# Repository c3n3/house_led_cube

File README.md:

# house_led_cube
LED Cube
digitalWrite

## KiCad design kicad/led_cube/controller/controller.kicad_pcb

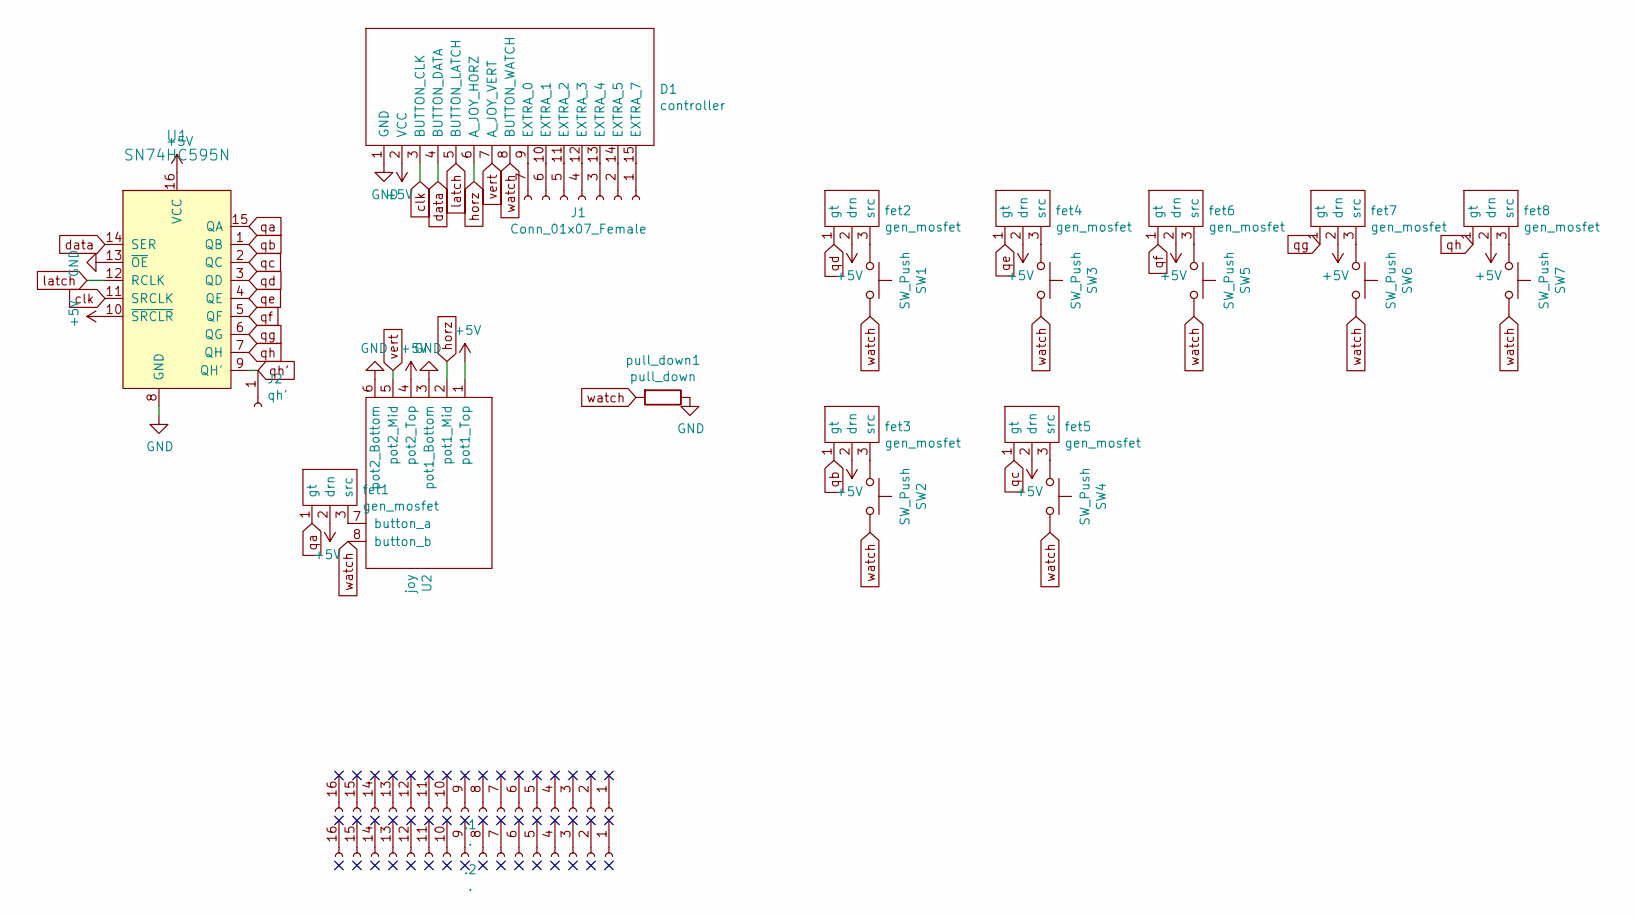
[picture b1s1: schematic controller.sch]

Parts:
.1, .2: .; proto
D1: controller; 15pin_controller
J1: Conn_01x07_Female; PinHeader_1x07_P2.54mm_Vertical
J2: qh'; PinHeader_1x01_P2.54mm_Horizontal
SW1, SW2, SW3, SW4, SW5, SW6, SW7: SW_Push; button
U1: SN74HC595N; MPN SN74HC595N; Digi-Key_PN 296-1600-5-ND
U2: joy
fet1, fet2, fet3, fet4, fet5, fet6, fet7, fet8: gen_mosfet; gen_fet
pull_down1: pull_down; R_Axial_DIN0207_L6.3mm_D2.5mm_P10.16mm_Horizontal

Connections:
+5V: D1.2 (VCC), U1.10 (~SRCLR), U1.16 (VCC), U2.1 (pot1_Top), U2.4 (pot2_Top), fet1.2 (drn), fet2.2 (drn), fet3.2 (drn), fet4.2 (drn), fet5.2 (drn), fet6.2 (drn), fet7.2 (drn), fet8.2 (drn)
GND: D1.1 (GND), U1.8 (GND), U1.13 (~OE), U2.3 (pot1_Bottom), U2.6 (pot2_Bottom), pull_down1.1
unnamed: D1.9 (EXTRA_0), J1.7
unnamed: D1.10 (EXTRA_1), J1.6
unnamed: D1.11 (EXTRA_2), J1.5
unnamed: D1.12 (EXTRA_3), J1.4
unnamed: D1.13 (EXTRA_4), J1.3
unnamed: D1.14 (EXTRA_5), J1.2
unnamed: D1.15 (EXTRA_7), J1.1
unnamed: SW1.1, fet2.3 (src)
unnamed: SW2.1, fet3.3 (src)
unnamed: SW3.1, fet4.3 (src)
unnamed: SW4.1, fet5.3 (src)
unnamed: SW5.1, fet6.3 (src)
unnamed: SW6.1, fet7.3 (src)
unnamed: SW7.1, fet8.3 (src)
unnamed: U2.7 (button_a), fet1.3 (src)
clk: D1.3 (BUTTON_CLK), U1.11 (SRCLK)
data: D1.4 (BUTTON_DATA), U1.14 (SER)
horz: D1.6 (A_JOY_HORZ), U2.2 (pot1_Mid)
latch: D1.5 (BUTTON_LATCH), U1.12 (RCLK)
qa: U1.15 (QA), fet1.1 (gt)
qb: U1.1 (QB), fet3.1 (gt)
qc: U1.2 (QC), fet5.1 (gt)
qd: U1.3 (QD), fet2.1 (gt)
qe: U1.4 (QE), fet4.1 (gt)
qf: U1.5 (QF), fet6.1 (gt)
qg: U1.6 (QG), fet7.1 (gt)
qh: U1.7 (QH), fet8.1 (gt)
qh': J2.1, U1.9 (QH')
vert: D1.7 (A_JOY_VERT), U2.5 (pot2_Mid)
watch: D1.8 (BUTTON_WATCH), SW1.2, SW2.2, SW3.2, SW4.2, SW5.2, SW6.2, SW7.2, U2.8 (button_b), pull_down1.2

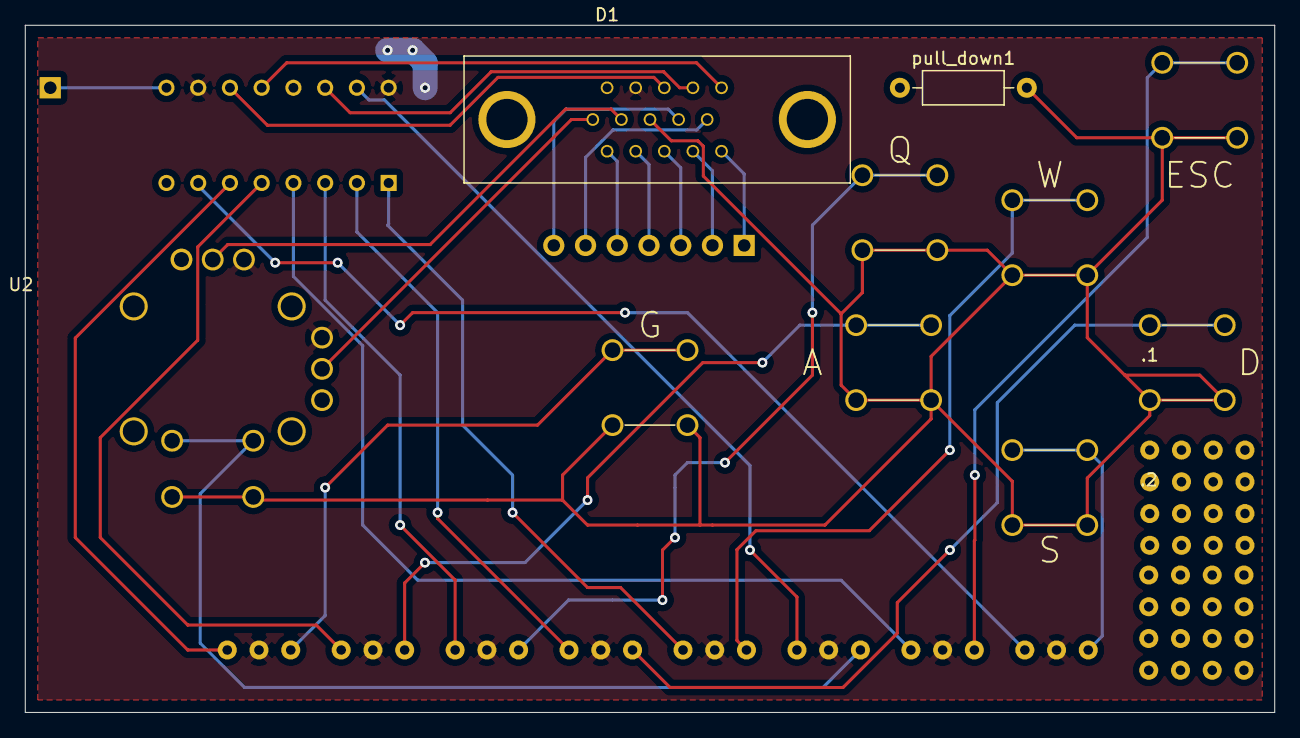
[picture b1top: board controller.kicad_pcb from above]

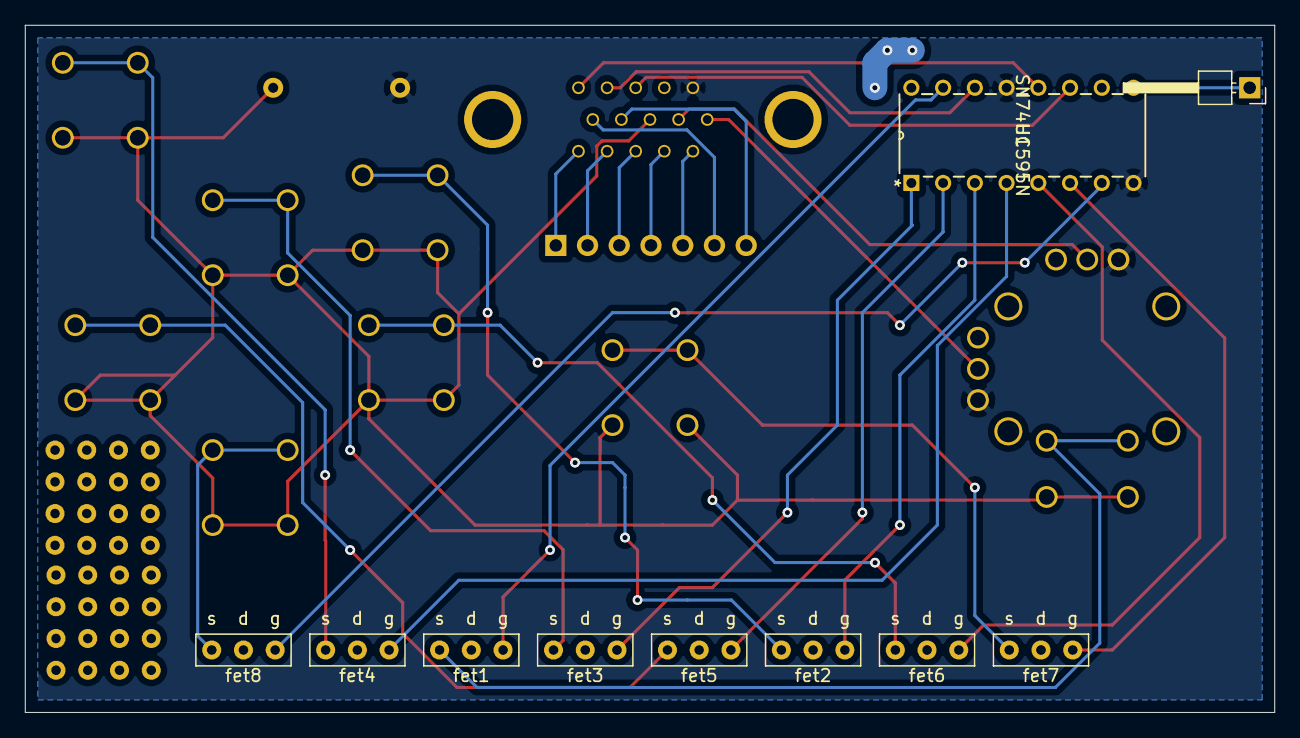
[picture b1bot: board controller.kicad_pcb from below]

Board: 2 copper layers, 100.0 x 55.0 mm, 23 parts (10 on the bottom side), 32 nets.

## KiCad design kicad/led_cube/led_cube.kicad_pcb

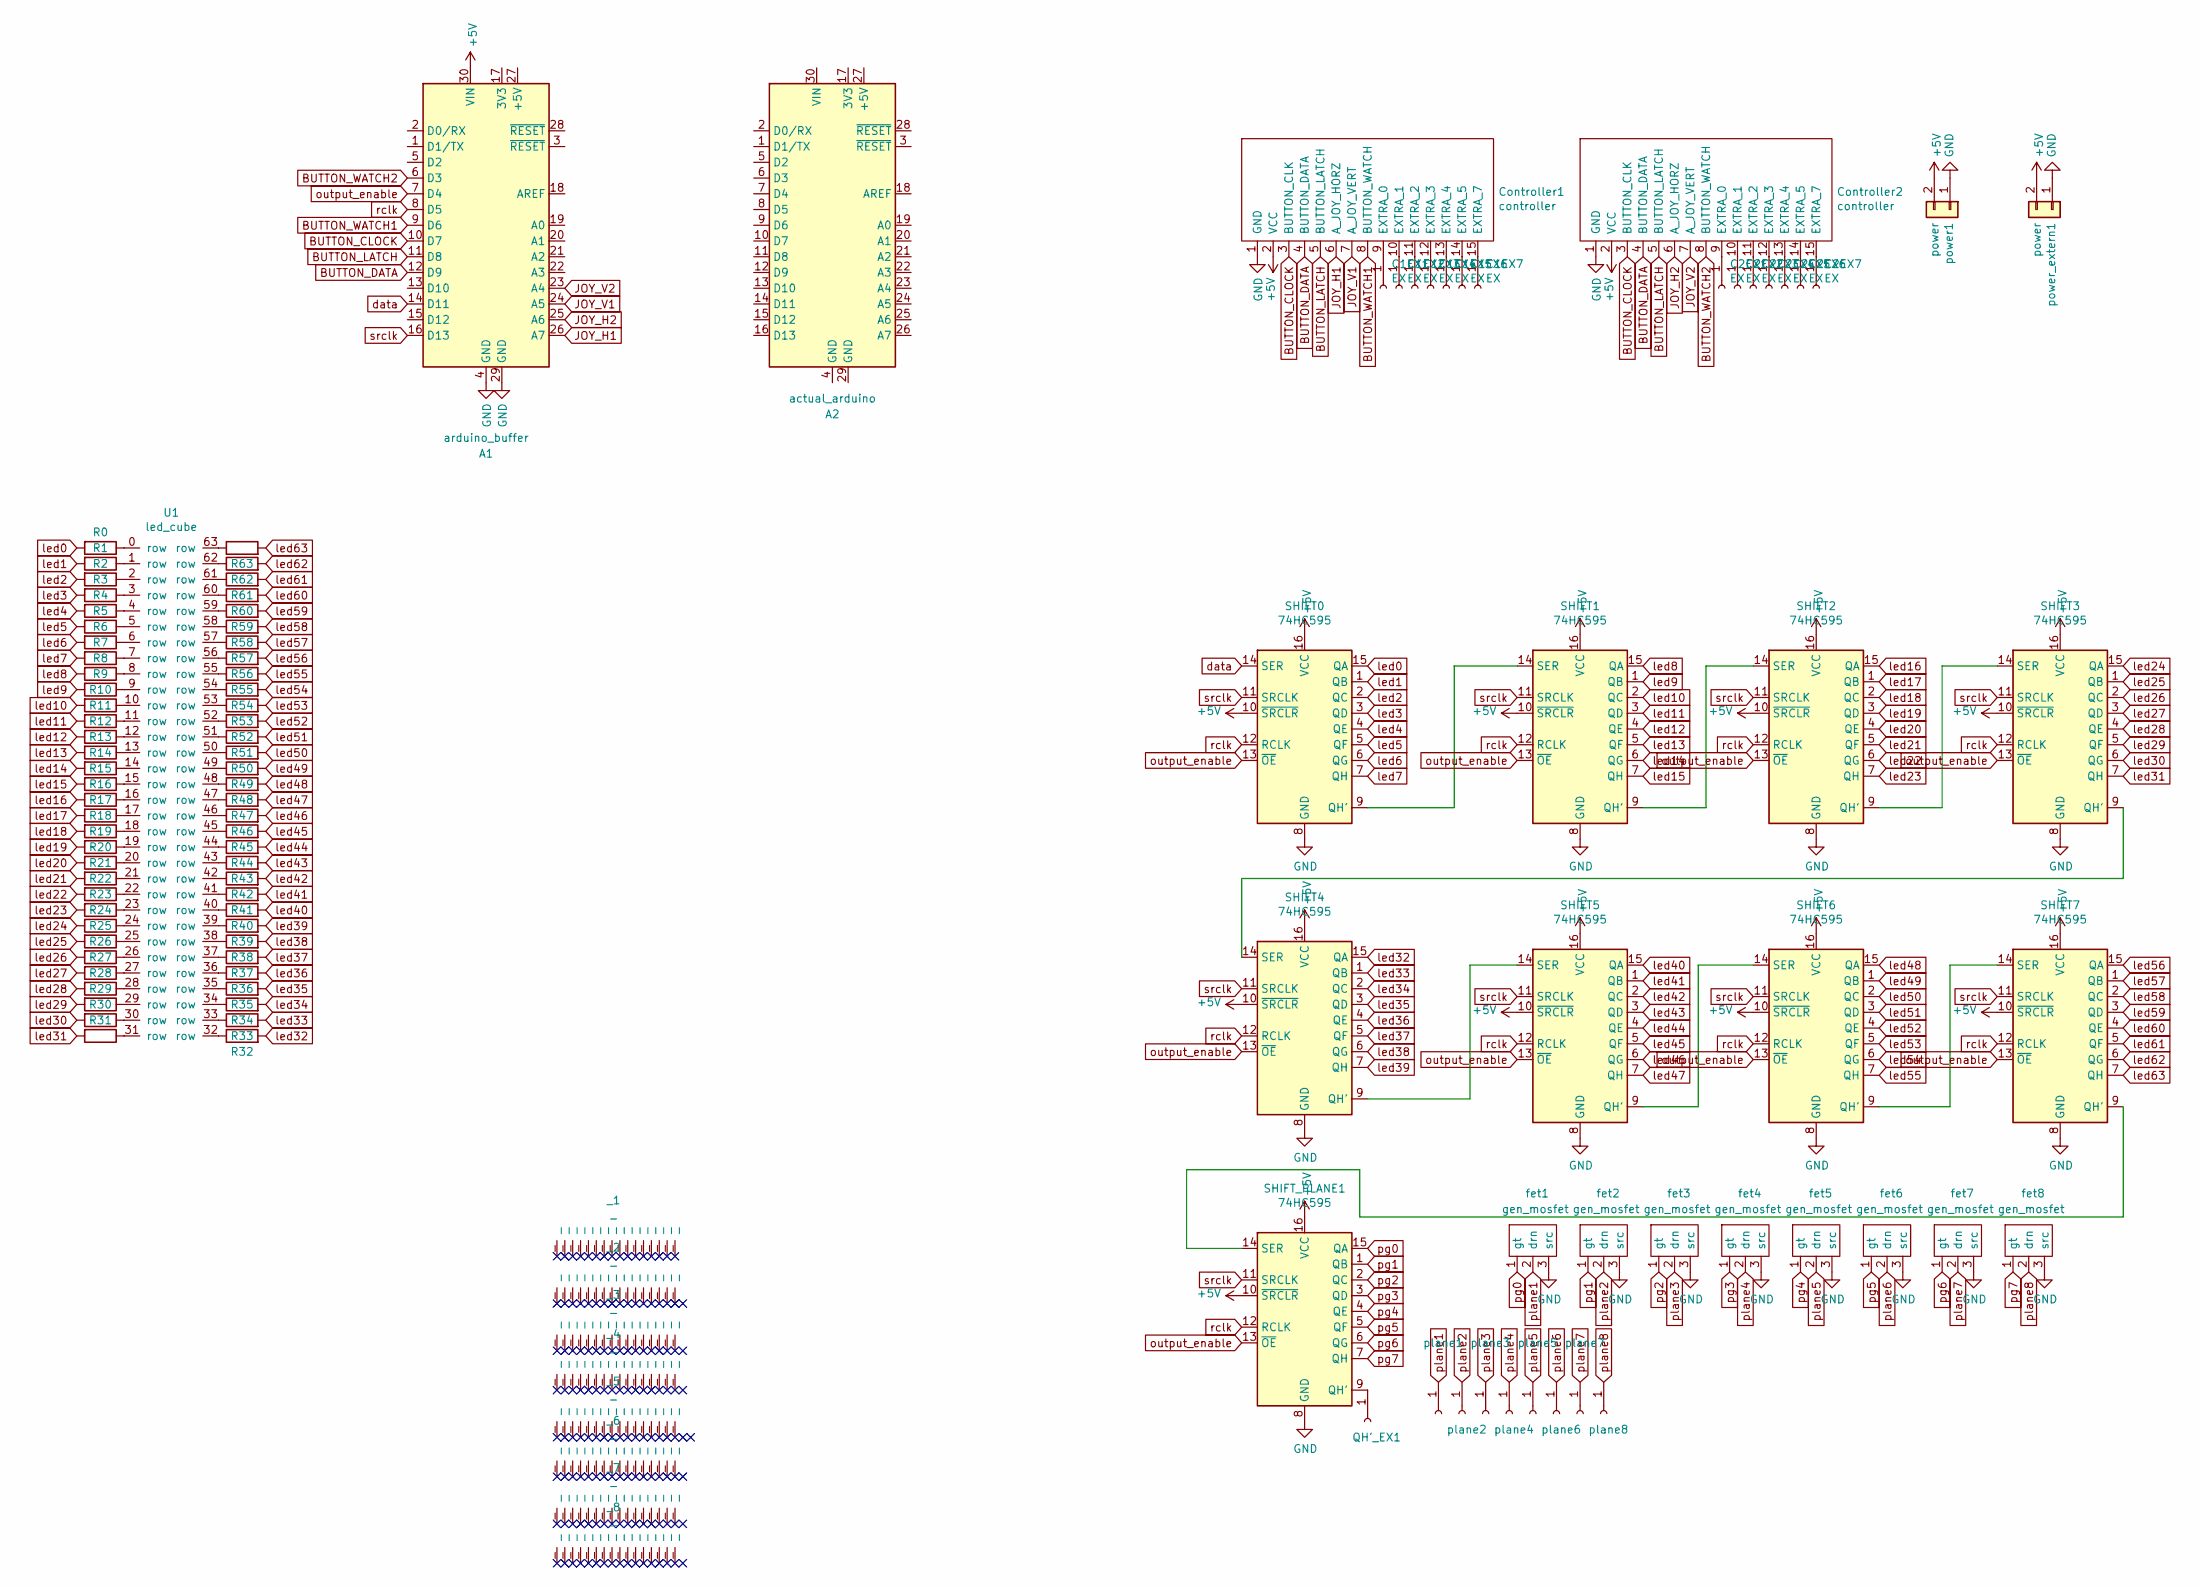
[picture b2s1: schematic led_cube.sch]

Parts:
A1: arduino_buffer; nano_buffer
A2: actual_arduino; nano
C1EX1, C1EX2, C1EX3, C1EX4, C1EX5, C1EX6, C1EX7, C2EX1, C2EX2, C2EX3, C2EX4, C2EX5, C2EX6, C2EX7: EX; PinHeader_1x01_P2.54mm_Vertical
Controller1, Controller2: controller; 15pin_controller
QH'_EX1: PinHeader_1x01_P2.54mm_Vertical
R0, R1, R2, R3, R4, R5, R6, R7, R8, R9, R10, R11, R12, R13, R14, R15, R16, R17, R18, R19, R20, R21, R22, R23, R24, R25, R26, R27, R28, R29, R30, R31, R32, R33, R34, R35, R36, R37, R38, R39, R40, R41, R42, R43, R44, R45, R46, R47, R48, R49, R50, R51, R52, R53, R54, R55, R56, R57, R58, R59, R60, R61, R62, R63: R_Axial_DIN0207_L6.3mm_D2.5mm_P7.62mm_Horizontal
SHIFT0, SHIFT1, SHIFT2, SHIFT3, SHIFT4, SHIFT5, SHIFT6, SHIFT7: 74HC595; SN74HC595N
SHIFT_PLANE1: 74HC595; SN74HC595N
U1: led_cube
_1, _2, _3, _4, _5, _6, _7, _8: _; proto
fet1, fet2, fet3, fet4, fet5, fet6, fet7, fet8: gen_mosfet; gen_fet
plane1, plane2, plane3, plane4, plane5, plane6, plane7, plane8: PinHeader_1x01_P2.54mm_Vertical
power1: power
power_extern1: power

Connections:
+5V: A1.30 (VIN), Controller1.2 (VCC), Controller2.2 (VCC), SHIFT0.10 (~SRCLR), SHIFT0.16 (VCC), SHIFT1.10 (~SRCLR), SHIFT1.16 (VCC), SHIFT2.10 (~SRCLR), SHIFT2.16 (VCC), SHIFT3.10 (~SRCLR), SHIFT3.16 (VCC), SHIFT4.10 (~SRCLR), SHIFT4.16 (VCC), SHIFT5.10 (~SRCLR), SHIFT5.16 (VCC), SHIFT6.10 (~SRCLR), SHIFT6.16 (VCC), SHIFT7.10 (~SRCLR), SHIFT7.16 (VCC), SHIFT_PLANE1.10 (~SRCLR), SHIFT_PLANE1.16 (VCC), power1.2, power_extern1.2
BUTTON_CLOCK: A1.10 (D7), Controller1.3 (BUTTON_CLK), Controller2.3 (BUTTON_CLK)
BUTTON_DATA: A1.12 (D9), Controller1.4 (BUTTON_DATA), Controller2.4 (BUTTON_DATA)
BUTTON_LATCH: A1.11 (D8), Controller1.5 (BUTTON_LATCH), Controller2.5 (BUTTON_LATCH)
BUTTON_WATCH1: A1.9 (D6), Controller1.8 (BUTTON_WATCH)
BUTTON_WATCH2: A1.6 (D3), Controller2.8 (BUTTON_WATCH)
GND: A1.4 (GND), A1.29 (GND), Controller1.1 (GND), Controller2.1 (GND), SHIFT0.8 (GND), SHIFT1.8 (GND), SHIFT2.8 (GND), SHIFT3.8 (GND), SHIFT4.8 (GND), SHIFT5.8 (GND), SHIFT6.8 (GND), SHIFT7.8 (GND), SHIFT_PLANE1.8 (GND), fet1.3 (src), fet2.3 (src), fet3.3 (src), fet4.3 (src), fet5.3 (src), fet6.3 (src), fet7.3 (src), fet8.3 (src), power1.1, power_extern1.1
JOY_H1: A1.26 (A7), Controller1.6 (A_JOY_HORZ)
JOY_H2: A1.25 (A6), Controller2.6 (A_JOY_HORZ)
JOY_V1: A1.24 (A5), Controller1.7 (A_JOY_VERT)
JOY_V2: A1.23 (A4), Controller2.7 (A_JOY_VERT)
unnamed: C1EX1.1, Controller1.9 (EXTRA_0)
unnamed: C1EX2.1, Controller1.10 (EXTRA_1)
unnamed: C1EX3.1, Controller1.11 (EXTRA_2)
unnamed: C1EX4.1, Controller1.12 (EXTRA_3)
unnamed: C1EX5.1, Controller1.13 (EXTRA_4)
unnamed: C1EX6.1, Controller1.14 (EXTRA_5)
unnamed: C1EX7.1, Controller1.15 (EXTRA_7)
unnamed: C2EX1.1, Controller2.9 (EXTRA_0)
unnamed: C2EX2.1, Controller2.10 (EXTRA_1)
unnamed: C2EX3.1, Controller2.11 (EXTRA_2)
unnamed: C2EX4.1, Controller2.12 (EXTRA_3)
unnamed: C2EX5.1, Controller2.13 (EXTRA_4)
unnamed: C2EX6.1, Controller2.14 (EXTRA_5)
unnamed: C2EX7.1, Controller2.15 (EXTRA_7)
unnamed: QH'_EX1.1, SHIFT_PLANE1.9 (QH')
unnamed: R0.1, U1.0
unnamed: R1.1, U1.1
unnamed: R2.1, U1.2
unnamed: R3.1, U1.3
unnamed: R4.1, U1.4
unnamed: R5.1, U1.5
unnamed: R6.1, U1.6
unnamed: R7.1, U1.7
unnamed: R8.1, U1.8
unnamed: R9.1, U1.9
unnamed: R10.1, U1.10
unnamed: R11.1, U1.11
unnamed: R12.1, U1.12
unnamed: R13.1, U1.13
unnamed: R14.1, U1.14
unnamed: R15.1, U1.15
unnamed: R16.1, U1.16
unnamed: R17.1, U1.17
unnamed: R18.1, U1.18
unnamed: R19.1, U1.19
unnamed: R20.1, U1.20
unnamed: R21.1, U1.21
unnamed: R22.1, U1.22
unnamed: R23.1, U1.23
unnamed: R24.1, U1.24
unnamed: R25.1, U1.25
unnamed: R26.1, U1.26
unnamed: R27.1, U1.27
unnamed: R28.1, U1.28
unnamed: R29.1, U1.29
unnamed: R30.1, U1.30
unnamed: R31.1, U1.31
unnamed: R32.1, U1.32
unnamed: R33.1, U1.33
unnamed: R34.1, U1.34
unnamed: R35.1, U1.35
unnamed: R36.1, U1.36
unnamed: R37.1, U1.37
unnamed: R38.1, U1.38
unnamed: R39.1, U1.39
unnamed: R40.1, U1.40
unnamed: R41.1, U1.41
unnamed: R42.1, U1.42
unnamed: R43.1, U1.43
unnamed: R44.1, U1.44
unnamed: R45.1, U1.45
unnamed: R46.1, U1.46
unnamed: R47.1, U1.47
unnamed: R48.1, U1.48
unnamed: R49.1, U1.49
unnamed: R50.1, U1.50
unnamed: R51.1, U1.51
unnamed: R52.1, U1.52
unnamed: R53.1, U1.53
unnamed: R54.1, U1.54
unnamed: R55.1, U1.55
unnamed: R56.1, U1.56
unnamed: R57.1, U1.57
unnamed: R58.1, U1.58
unnamed: R59.1, U1.59
unnamed: R60.1, U1.60
unnamed: R61.1, U1.61
unnamed: R62.1, U1.62
unnamed: R63.1, U1.63
unnamed: SHIFT0.9 (QH'), SHIFT1.14 (SER)
unnamed: SHIFT1.9 (QH'), SHIFT2.14 (SER)
unnamed: SHIFT2.9 (QH'), SHIFT3.14 (SER)
unnamed: SHIFT3.9 (QH'), SHIFT4.14 (SER)
unnamed: SHIFT4.9 (QH'), SHIFT5.14 (SER)
unnamed: SHIFT5.9 (QH'), SHIFT6.14 (SER)
unnamed: SHIFT6.9 (QH'), SHIFT7.14 (SER)
unnamed: SHIFT7.9 (QH'), SHIFT_PLANE1.14 (SER)
data: A1.14 (D11), SHIFT0.14 (SER)
led0: R0.2, SHIFT0.15 (QA)
led1: R1.2, SHIFT0.1 (QB)
led2: R2.2, SHIFT0.2 (QC)
led3: R3.2, SHIFT0.3 (QD)
led4: R4.2, SHIFT0.4 (QE)
led5: R5.2, SHIFT0.5 (QF)
led6: R6.2, SHIFT0.6 (QG)
led7: R7.2, SHIFT0.7 (QH)
led8: R8.2, SHIFT1.15 (QA)
led9: R9.2, SHIFT1.1 (QB)
led10: R10.2, SHIFT1.2 (QC)
led11: R11.2, SHIFT1.3 (QD)
led12: R12.2, SHIFT1.4 (QE)
led13: R13.2, SHIFT1.5 (QF)
led14: R14.2, SHIFT1.6 (QG)
led15: R15.2, SHIFT1.7 (QH)
led16: R16.2, SHIFT2.15 (QA)
led17: R17.2, SHIFT2.1 (QB)
led18: R18.2, SHIFT2.2 (QC)
led19: R19.2, SHIFT2.3 (QD)
led20: R20.2, SHIFT2.4 (QE)
led21: R21.2, SHIFT2.5 (QF)
led22: R22.2, SHIFT2.6 (QG)
led23: R23.2, SHIFT2.7 (QH)
led24: R24.2, SHIFT3.15 (QA)
led25: R25.2, SHIFT3.1 (QB)
led26: R26.2, SHIFT3.2 (QC)
led27: R27.2, SHIFT3.3 (QD)
led28: R28.2, SHIFT3.4 (QE)
led29: R29.2, SHIFT3.5 (QF)
led30: R30.2, SHIFT3.6 (QG)
led31: R31.2, SHIFT3.7 (QH)
led32: R32.2, SHIFT4.15 (QA)
led33: R33.2, SHIFT4.1 (QB)
led34: R34.2, SHIFT4.2 (QC)
led35: R35.2, SHIFT4.3 (QD)
led36: R36.2, SHIFT4.4 (QE)
led37: R37.2, SHIFT4.5 (QF)
led38: R38.2, SHIFT4.6 (QG)
led39: R39.2, SHIFT4.7 (QH)
led40: R40.2, SHIFT5.15 (QA)
led41: R41.2, SHIFT5.1 (QB)
led42: R42.2, SHIFT5.2 (QC)
led43: R43.2, SHIFT5.3 (QD)
led44: R44.2, SHIFT5.4 (QE)
led45: R45.2, SHIFT5.5 (QF)
led46: R46.2, SHIFT5.6 (QG)
led47: R47.2, SHIFT5.7 (QH)
led48: R48.2, SHIFT6.15 (QA)
led49: R49.2, SHIFT6.1 (QB)
led50: R50.2, SHIFT6.2 (QC)
led51: R51.2, SHIFT6.3 (QD)
led52: R52.2, SHIFT6.4 (QE)
led53: R53.2, SHIFT6.5 (QF)
led54: R54.2, SHIFT6.6 (QG)
led55: R55.2, SHIFT6.7 (QH)
led56: R56.2, SHIFT7.15 (QA)
led57: R57.2, SHIFT7.1 (QB)
led58: R58.2, SHIFT7.2 (QC)
led59: R59.2, SHIFT7.3 (QD)
led60: R60.2, SHIFT7.4 (QE)
led61: R61.2, SHIFT7.5 (QF)
led62: R62.2, SHIFT7.6 (QG)
led63: R63.2, SHIFT7.7 (QH)
output_enable: A1.7 (D4), SHIFT0.13 (~OE), SHIFT1.13 (~OE), SHIFT2.13 (~OE), SHIFT3.13 (~OE), SHIFT4.13 (~OE), SHIFT5.13 (~OE), SHIFT6.13 (~OE), SHIFT7.13 (~OE), SHIFT_PLANE1.13 (~OE)
pg0: SHIFT_PLANE1.15 (QA), fet1.1 (gt)
pg1: SHIFT_PLANE1.1 (QB), fet2.1 (gt)
pg2: SHIFT_PLANE1.2 (QC), fet3.1 (gt)
pg3: SHIFT_PLANE1.3 (QD), fet4.1 (gt)
pg4: SHIFT_PLANE1.4 (QE), fet5.1 (gt)
pg5: SHIFT_PLANE1.5 (QF), fet6.1 (gt)
pg6: SHIFT_PLANE1.6 (QG), fet7.1 (gt)
pg7: SHIFT_PLANE1.7 (QH), fet8.1 (gt)
plane1: fet1.2 (drn), plane1.1
plane2: fet2.2 (drn), plane2.1
plane3: fet3.2 (drn), plane3.1
plane4: fet4.2 (drn), plane4.1
plane5: fet5.2 (drn), plane5.1
plane6: fet6.2 (drn), plane6.1
plane7: fet7.2 (drn), plane7.1
plane8: fet8.2 (drn), plane8.1
rclk: A1.8 (D5), SHIFT0.12 (RCLK), SHIFT1.12 (RCLK), SHIFT2.12 (RCLK), SHIFT3.12 (RCLK), SHIFT4.12 (RCLK), SHIFT5.12 (RCLK), SHIFT6.12 (RCLK), SHIFT7.12 (RCLK), SHIFT_PLANE1.12 (RCLK)
srclk: A1.16 (D13), SHIFT0.11 (SRCLK), SHIFT1.11 (SRCLK), SHIFT2.11 (SRCLK), SHIFT3.11 (SRCLK), SHIFT4.11 (SRCLK), SHIFT5.11 (SRCLK), SHIFT6.11 (SRCLK), SHIFT7.11 (SRCLK), SHIFT_PLANE1.11 (SRCLK)

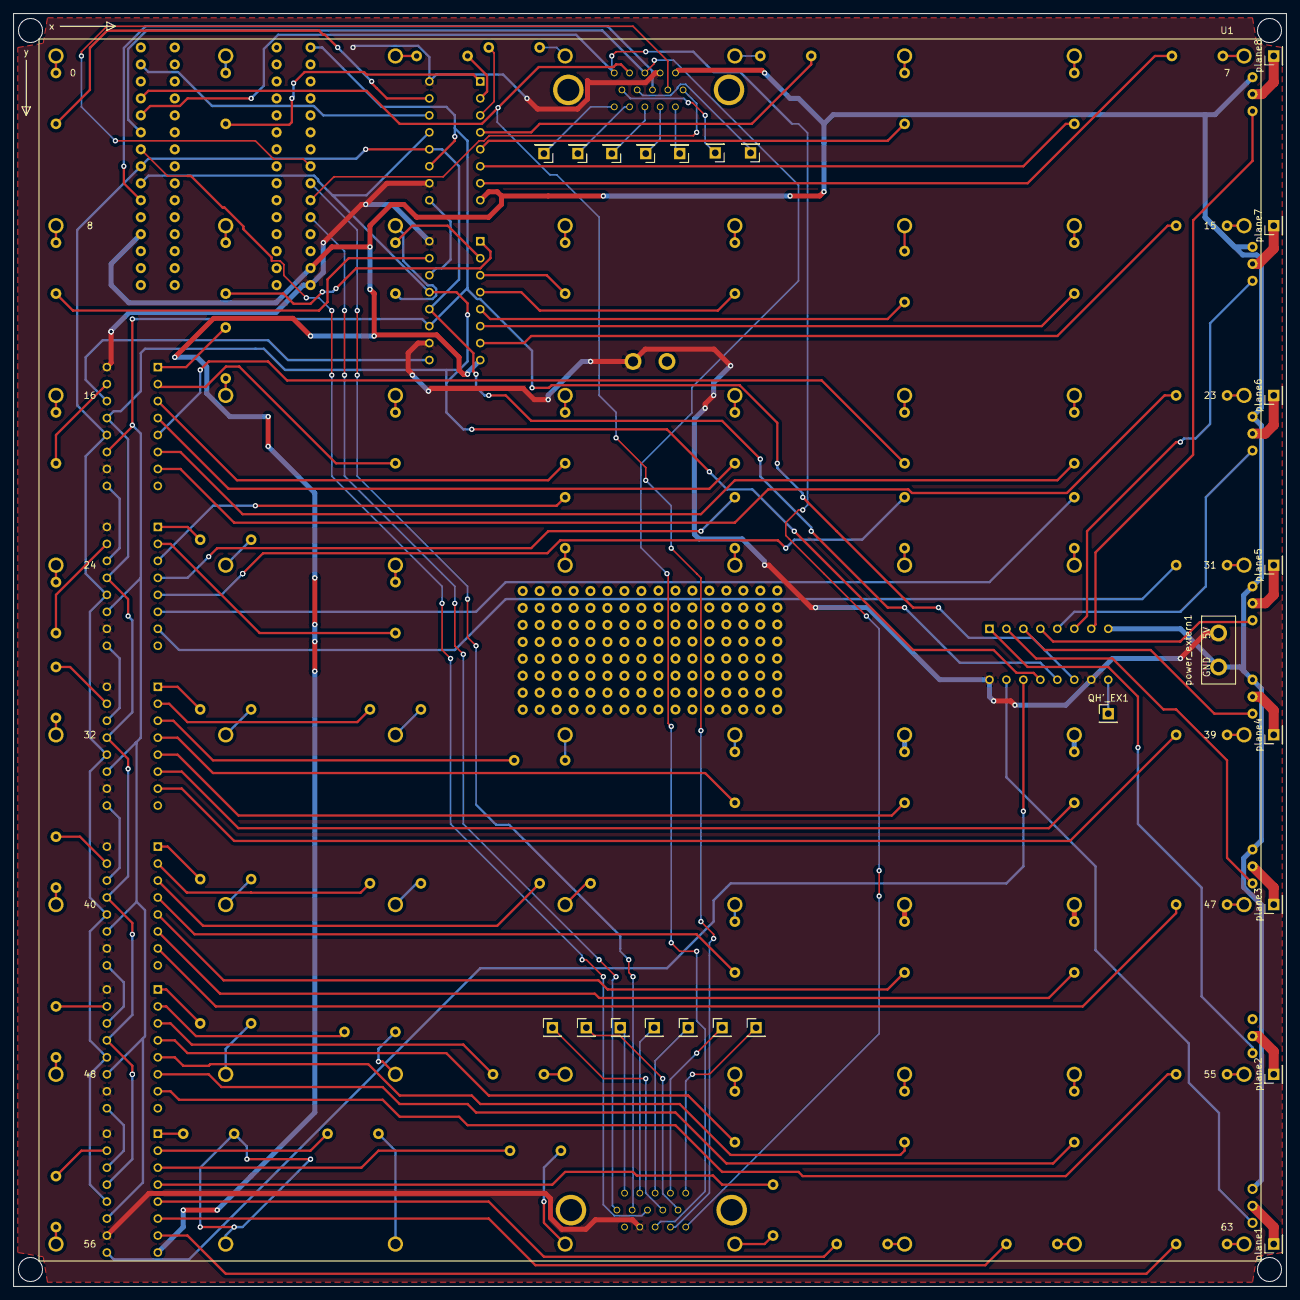
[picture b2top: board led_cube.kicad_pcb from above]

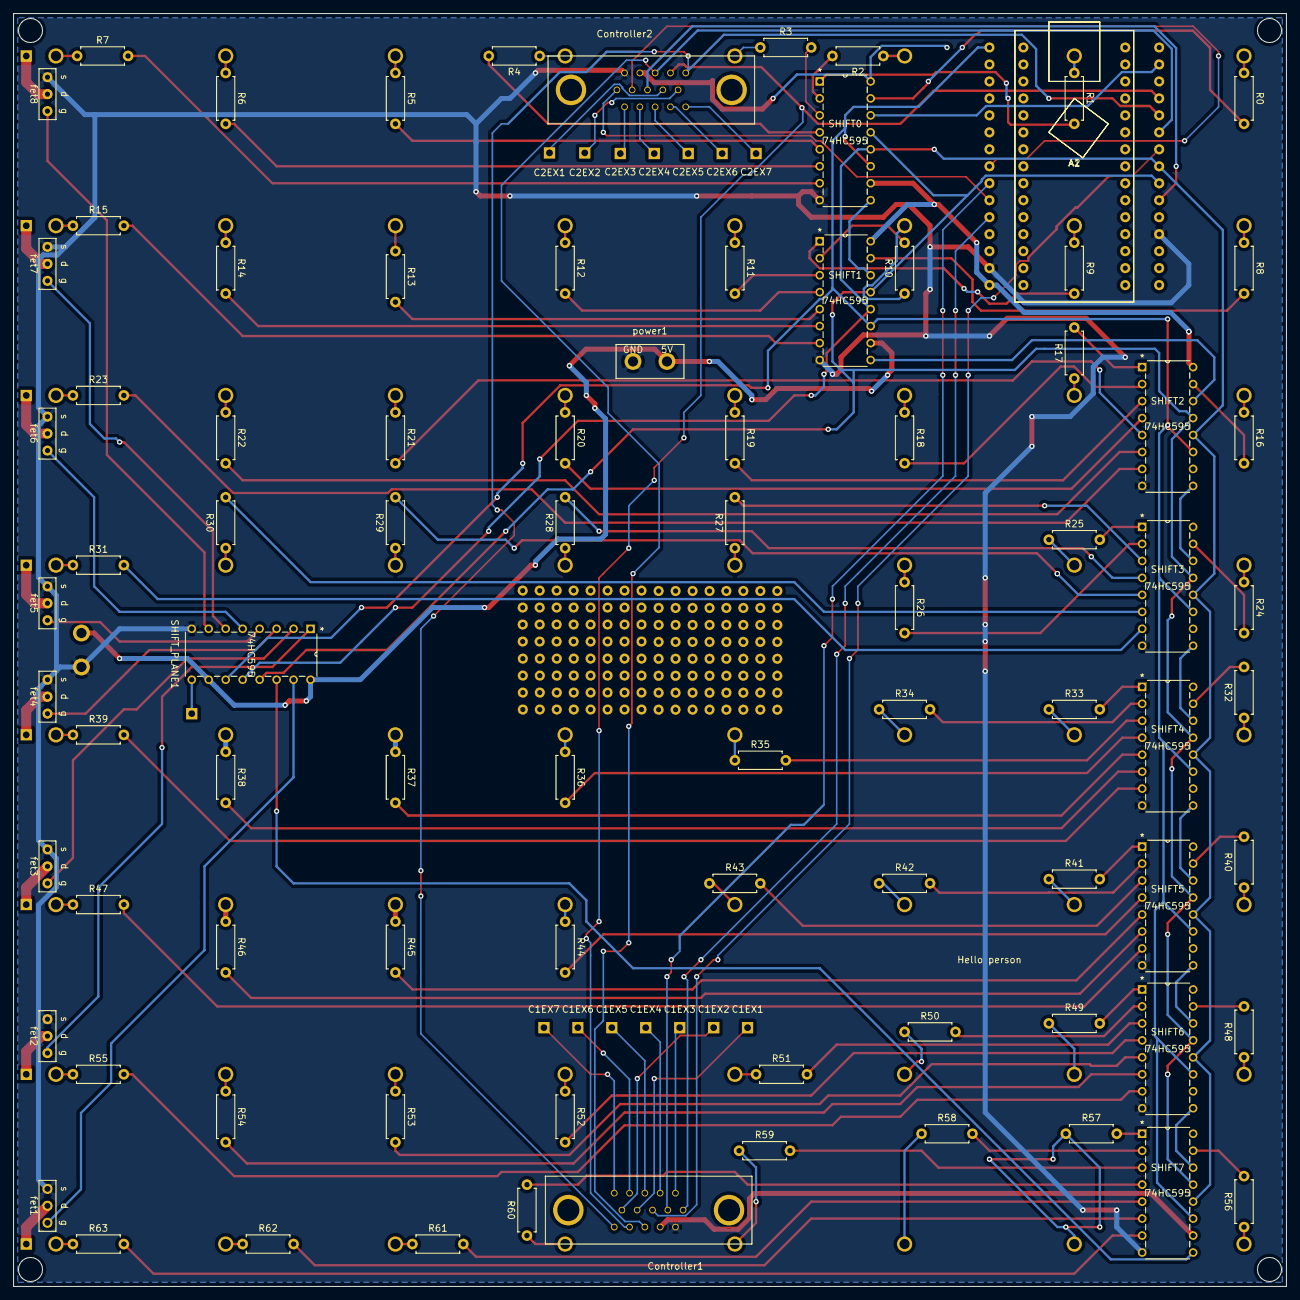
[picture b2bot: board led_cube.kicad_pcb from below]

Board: 2 copper layers, 190.5 x 190.5 mm, 119 parts (86 on the bottom side), 182 nets.

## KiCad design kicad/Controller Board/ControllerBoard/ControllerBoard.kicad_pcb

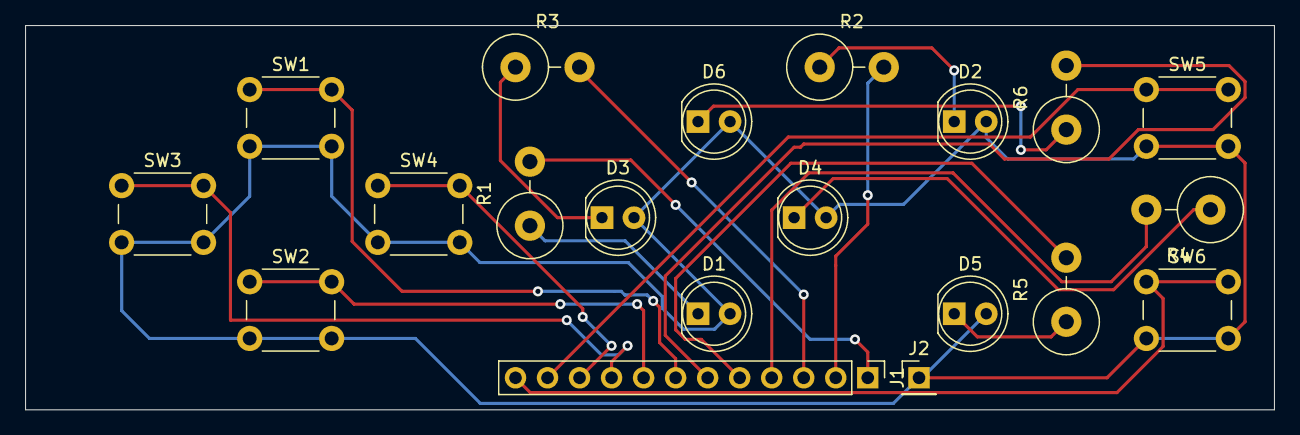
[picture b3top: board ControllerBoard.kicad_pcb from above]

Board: 2 copper layers, 99.1 x 30.5 mm, 20 parts (0 on the bottom side), 19 nets.

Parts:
D1, D2, D3, D4, D5, D6: LED; LED_D5.0mm
J1: Conn_01x12_Male; PinHeader_1x12_P2.54mm_Vertical
J2: Conn_01x01_Male; PinHeader_1x01_P2.54mm_Vertical
R1, R2, R3, R4, R5, R6: R; R_Axial_DIN0516_L15.5mm_D5.0mm_P5.08mm_Vertical
SW1: Up; SW_PUSH_6mm_H5mm
SW2: Down; SW_PUSH_6mm_H5mm
SW3: Left; SW_PUSH_6mm_H5mm
SW4: Right; SW_PUSH_6mm_H5mm
SW5: Forward; SW_PUSH_6mm_H5mm
SW6: Backwards; SW_PUSH_6mm_H5mm

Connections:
Backwards: J1.12, SW6.1
Down: J1.8, SW2.1
Froward: J1.11, SW5.1
GND: D1.2, D2.2, D3.2, D4.2, D5.2, D6.2, J2.1, SW1.2, SW2.2, SW3.2, SW4.2, SW5.2, SW6.2
LED1: J1.1, R1.2
LED2: J1.2, R2.2
LED3: J1.3, R3.2
LED4: J1.4, R4.2
LED5: J1.5, R5.2
LED6: J1.6, R6.2
Left: J1.9, SW3.1
unnamed: D1.1, R1.1
unnamed: D2.1, R2.1
unnamed: D3.1, R3.1
unnamed: D4.1, R4.1
unnamed: D5.1, R5.1
unnamed: D6.1, R6.1
Right: J1.10, SW4.1
Up: J1.7, SW1.1

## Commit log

2020-09-06 Added solid works starter
2020-09-06 i typed digitalWrite
2020-09-06 Added kicad files folder
2020-09-08 Controller for 3D snake
2020-09-08 Solidworks LED Cube
2020-09-11 Solid works switch
2020-09-13 The led cube kicad is growing
2020-09-15 Added cpp
2020-09-15 Added more code
2020-09-15 Code has been started
2020-09-20 Added code and new 8x4 array in solid works
2020-10-19 Stuff
2020-12-03 Added stuff
2020-12-08 Added lots of stuff
2020-12-13 Added lots
2020-12-31 Added someThings?
2021-01-01 SAMD boards now work flawlessly
2021-03-05 restructure
2021-03-05 More
2021-04-07 Alot of stuff

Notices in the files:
parts and their libraries:
Copyright 2016 Accelerated Designs. All rights reserved.
